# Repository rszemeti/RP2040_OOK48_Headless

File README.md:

# OOK48 Headless Serial + Desktop GUI

A modified RP2350/RP2040 OOK48 build where the touchscreen UI is replaced by a USB serial
control path and a desktop Python GUI.

All spectrum/waterfall rendering, operating controls, decode display, message management, and logging move to the PC GUI.

## Quick Links

- Latest release (download `.exe` / `.uf2`): https://github.com/rszemeti/RP2040_OOK48_Headless/releases/latest

## GUI (Front and Center)

The GUI is now the primary operator interface:

- **Live decode console** with RX/TX/error colouring and UTC timestamps
- **Contest TX pad** with dynamic templates (`{myCall}`, `{theirCall}`, `{serial}`, `{loc}`)
- **Confidence-aware decode pipeline** with unknown-gating and accumulator state display
- **Waterfall controls** (clip, auto-scale, clear) and decode mode quick-toggle
- **Persistent config** for callsign, timing, mode, and TX templates

---

## Performance vs Single-Repeat Decode

The firmware stream is effectively single-repeat per symbol period, but the GUI adds a
**soft-accumulator repeat** on top of that data:

- single-repeat characters are shown immediately (fast feedback)
- repeated cycles are accumulated per position and re-decoded with improved confidence
- unstable copy can be promoted to stable copy once mean confidence rises
- low-confidence runs auto-collapse and reset cleanly

This gives a practical improvement in weak/marginal conditions without changing the
core RF/FFT/radio processing code.

Current confidence gates used by the GUI accumulator:

- per-character unknown gate: `0.180` (below this, symbol is treated as unknown)
- confirmed-copy threshold: `0.65` (mean confidence)
- collapse threshold: `0.25` for `3` consecutive cycles

### Expected decode levels (measured)

Normal mode (good copy guideline):

- 1 repeat: `-17`
- 2 repeats: `-19`
- 4 repeats: `-20`
- 8 repeats: `-21`

Rainscatter mode (good copy guideline):

- 1 repeat: `+5 dB`
- 2 repeats: `+3 dB`
- 4 repeats: `+2 dB`
- 8 repeats: `+1.5 dB`

---

## Rainscatter Mode (Decode Mode 2)

`SET:decmode:2` enables **Rainscatter** mode, which uses wideband power behaviour
intended for bursty/scatter conditions rather than stable narrowband copy.

Operationally:

- firmware switches to decode mode `2`
- GUI can toggle Normal/Rainscatter from the RX pane button
- if connected firmware does not support mode `2`, GUI falls back to Normal safely

Use Rainscatter when copy is intermittent and burst-dominated; use Normal for steady
paths.

---

## What Changed From the Original

### Removed Entirely
- `config.ino` — replaced by serial `SET:` commands
- `GetApp.ino` — app selection now via `SET:app:`
- `MemPad.ino` — message slot selection now via `CMD:txmsg:`
- `TextPad.ino` — message text entry now via Python GUI
- `USBDrive.ino` — SD card logging is handled by the Python GUI instead
- All SD card hardware support (`SdFat`, `Adafruit_TinyUSB`, SPI1 setup)
- EEPROM read/write — settings are held in RAM and pushed from Python on connect
- Battery voltage measurement and calibration
- All touchscreen UI — buttons, config pages, keyboard, memory pad

### Modified
- `RP2040_OOK48_Serial.ino` — main file rewritten for RP2350/RP2040 targets: serial protocol added,
  `defaultSettings()` replaces EEPROM load/save, LCD init simplified
- `globals.h` — SD, battery, and EEPROM-specific variables removed;
  `core0Ready` flag added for core synchronisation
- `GUI.ino` — stripped to spectrum/waterfall/legend drawing only
- `DEFINES.h` — SD card pin definitions removed

### Unchanged
- `DMA.ino`, `FFT.ino`, `Rx.ino`, `Tx.ino`, `JT4Decode.ino`,
  `PI4Decode.ino`, `fano.ino` — all radio processing untouched

---

## How It Works

The RP2350/RP2040 enumerates as a USB CDC serial device (virtual COM port) when connected
to a laptop. The Python GUI connects to this port at 115200 baud.

On boot the firmware applies safe defaults and sends `RDY:<version>`. The Python
GUI responds by pushing all configuration settings. From that point on, decoded
messages stream out as simple prefixed ASCII lines and the GUI sends commands back
as needed.

The LCD shows the spectrum and waterfall continuously during RX, and a red TX
indicator during transmit — exactly as before, just without anything else on screen.

Protocol details for firmware/GUI integration are in `gui/ook48_serial_protocol.md`
and `Documents/ook48_serial_protocol.md`.

### Core-to-core FIFO char payload convention

To avoid races when Core 0 produces character events faster than Core 1 can consume them,
character-bearing FIFO messages are packed into one 32-bit word:

- low 16 bits: Core1Message command ID
- high 16 bits: associated character payload (8-bit char value)

Helpers are defined in `arduino/include/globals.h`:

- `FIFO_COMMAND(word)`
- `PACK_FIFO_CHAR(cmd, ch)`
- `UNPACK_FIFO_CHAR(word)`

Current packed char messages:

- `MORSEMESSAGE`
- `MESSAGE`
- `TMESSAGE`

This prevents shared-variable overwrite issues (for example, Morse CHAR followed quickly by WORD_SEP)
because command and payload travel atomically in the same FIFO entry.

---

## Firmware Releases (UF2)

For RP2350/RP2040 Pico-class targets, the easiest install format is **UF2** (not `avrdude`).

### RP2350 boards replacing RP2040

New Pico-compatible boards are increasingly RP2350-based and are generally the default choice now.
For this project, treat RP2350 as the modern replacement for RP2040: use the same UF2 workflow,
and keep using RP2040 hardware where already deployed.

### Download latest release assets

1. Open the project **Releases** page on GitHub:
  - https://github.com/rszemeti/RP2040_OOK48_Headless/releases/latest
2. Open the newest release (top of the list).
3. Under **Assets**, download:
  - `*.uf2` (firmware for the RP2350/RP2040 board)
  - `OOK48_GUI.exe` (Windows desktop GUI)

If Windows warns about SmartScreen, click **More info** → **Run anyway**.

### Flash UF2 to RP2350/RP2040 (BOOTSEL method)

1. Unplug the RP2350/RP2040 board from USB.
2. Press and hold the **BOOTSEL** button (some boards label this as **BOOT**).
3. While still holding BOOTSEL, plug the USB cable into the PC.
4. Release BOOTSEL after the board appears as a USB drive named **RPI-RP2**.
5. Drag/copy the downloaded `*.uf2` file onto that **RPI-RP2** drive.
6. Wait a few seconds; the drive disconnects automatically and the board reboots into the new firmware.

If your board has a separate **RESET/RUN** button, you typically still need to hold **BOOTSEL** (not RESET) during plug-in to enter UF2 bootloader mode.

---

### Windows 

The easiest solution for running the GUI on Winows is to download our "one file" release.

- `dist/OOK48_GUI.exe`

This is a prebuilt GUI instead of running all the Python stuff locally, just download `OOK48_GUI.exe` from the latest GitHub Release assets (see **Download latest release assets** above).

For local one-file builds with metadata stamping:

```powershell
.\scripts\build_gui_release.ps1
```

This script now auto-generates `assets/windows_version.txt` before calling PyInstaller.
Version fields are derived from Git (`tag`/`commit count`, with commit SHA/date in metadata comments).

## Python GUI

If you want to fiddle with the GUI and make changes, running the rawPython version is for you.

- **`ook48_gui.py`** — standard GUI with waterfall

### Requirements
```
pip install -r gui/requirements.txt
```

### Running
```
python ook48_gui.py
```

### Features

**Connection bar** — port selector, connect/disconnect, GPS time and locator
displayed live from `STA:` updates.

**Decode / TX tab** — split vertically into RX (left) and TX (right) panes.

- **RX pane** — colour-coded decode output: green=RX, red=TX echo, orange=error,
  dark green=JT4, purple=PI4, grey=system. Each message is prefixed with a UTC
  timestamp when its first character arrives. Double-clicking any received (green)
  word sets it as "Their call" in the TX pane.
  Clear button clears the screen only — the log file is unaffected.
  Save Log writes the current screen content to a file.

- **TX pane — Contest QSO pad** — designed for rapid contest operation:
  - **My call** — your callsign, persisted between sessions
  - **Their call** — type or double-click a received callsign to populate
  - **Serial #** — contest serial number with +1 button, persisted between sessions
  - All fields update the 10 slot buttons live as you type
  - **Single click** on any slot button immediately transmits that slot
  - **■ STOP TX** halts transmission and returns to RX

**TX message slots** — 10 slots are template-driven and rendered live from your
current operating fields.

The default slot template set:

| Slot | Content |
|------|---------|
| 0 | `CQ {myCall}` |
| 1 | `{theirCall} DE {myCall}` |
| 2 | `{theirCall} 59{serial} {loc}` |
| 3 | `{theirCall} 59{serial}` |
| 4 | `{loc}` |
| 5 | `ALL AGN` |
| 6 | `LOC AGN` |
| 7 | `RPT AGN` |
| 8 | `RGR 73` |
| 9 | `{myCall}` |

`{loc}` is substituted with live GPS locator data from `STA:`. Other substitutions are
rendered in the GUI before sending each slot to firmware.

Templates are user-editable in `ook48_config.json` (`messages[]`) and can be changed
without touching code.

**Settings tab** — all firmware parameters with Apply, Save, and Reboot buttons.

**File logging** — everything shown in the decode window is also written to
`ook48_YYYYMMDD.log` in the same directory, opened automatically on startup.
Multiple sessions on the same day append to the same file with a session marker.

### Waterfall (ook48_waterfall.py only)

A waterfall display sits above the decode text in the RX pane. It renders `WF:`
lines from the firmware as a scrolling thermal colour map (black → blue → cyan →
green → yellow → red).

- **Min / Max** spinboxes clip the colour range to the interesting signal level
- **Auto** sets Min/Max from the actual data range
- **Clear WF** clears the waterfall history
- **▶ Fake WF** generates synthetic test data at 9 rows/second — useful for
  testing the display without hardware connected

The waterfall adapts automatically to however many bins the firmware sends and
scales horizontally to fill the available window width.

### Config file (`ook48_config.json`)

Created automatically on first run. Persists port, callsign, serial number, and
all firmware settings between sessions. Example:

```json
{
  "port": "COM3",
  "callsign": "G4EML",
  "serial": 1,
  "gpsbaud": 9600,
  "loclen": 8,
  "decmode": 0,
  "txadv": 0,
  "rxret": 0,
  "halfrate": 0,
  "app": 0,
  "messages": [
    "CQ {myCall}",
    "{theirCall} DE {myCall}",
    "{theirCall} 59{serial} {loc}",
    "{theirCall} 59{serial}",
    "{loc}",
    "ALL AGN",
    "LOC AGN",
    "RPT AGN",
    "RGR 73",
    "{myCall}"
  ]
}
```

---

## Credits

- Colin Durbridge (G4EML) — original OOK48 work
- Robin Szemeti (G1YFG) — RP2040_OOK48_Headless (RP2350/RP2040) serial + GUI adaptation

---

## Notes

**GPS locator** — the locator shown in the connection bar is received from the
firmware via `STA:` lines and is used live in the TX slot buttons. If GPS has not
yet locked, `{LOC}` is passed through to the firmware for its own substitution.

**GPS baud rate** — `autoBaud()` detection is removed. The firmware starts at 9600
by default. If your GPS module runs at 38400, change `gpsbaud` in `ook48_config.json`
before first connect, or set it in the Settings tab and click Apply.

**First connect** — there is a 1.5 second delay after connecting before the config
push is sent, to allow the firmware time to finish booting and send its `RDY:` message.

**App switching** — changing the app via `SET:app:` causes an immediate reboot. The
Python GUI will show a disconnect; simply reconnect after a few seconds.

**TX echo** — transmitted characters are echoed back by the firmware as `TX:` lines
and appear in red in the decode window as they are actually sent, one character at
a time.

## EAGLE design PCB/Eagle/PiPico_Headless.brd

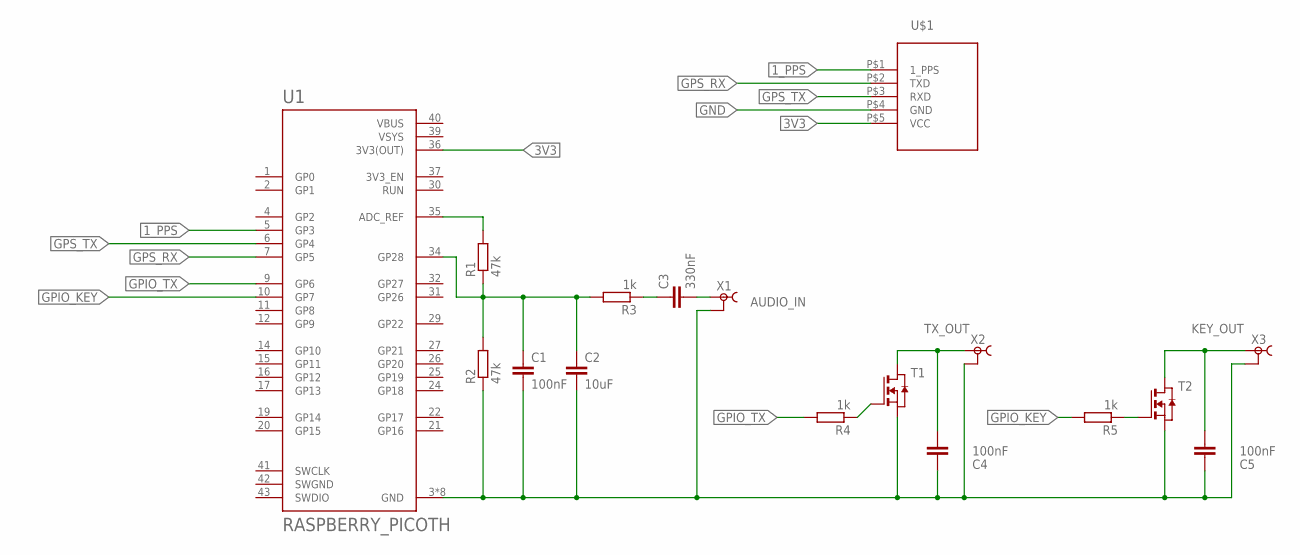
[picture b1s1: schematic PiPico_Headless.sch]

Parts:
C1, C4, C5: 100nF; C0805
C2: 10uF; C0805
C3: 330nF; C0805
R1, R2: 47k; R0805
R3, R4, R5: 1k; R0805
T1, T2: NMOSSOT23; SOT-23
U1: RASPBERRY_PICOTH; PICO-PKG-TH
U$1: GPS
X1: AUDIO_IN; TOBU3
X2: TX_OUT; TOBU3
X3: KEY_OUT; TOBU3; MPN TOBU 3

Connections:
1_PPS: U1.5 (GP3), U$1.P$1 (1_PPS)
3V3: U1.36 (3V3(OUT)), U$1.P$5 (VCC)
GND: C1.2, C2.2, C4.1, C5.1, R2.1, T1.2 (S), T2.2 (S), U1.3 (GND), U1.8 (GND), U1.13 (GND), U1.18 (GND), U1.23 (GND), U1.28 (GND), U1.33 (GND), U1.38 (GND), U$1.P$4 (GND), X1.2, X1.2@1 (2), X1.2@2 (2), X2.2, X2.2@1 (2), X2.2@2 (2), X3.2, X3.2@1 (2), X3.2@2 (2)
GPIO_KEY: R5.2, U1.10 (GP7)
GPIO_TX: R4.2, U1.9 (GP6)
GPS_RX: U1.7 (GP5), U$1.P$2 (TXD)
GPS_TX: U1.6 (GP4), U$1.P$3 (RXD)
unnamed: C1.1, C2.1, R1.1, R2.2, R3.2, U1.34 (GP28)
unnamed: R5.1, T2.3 (G)
unnamed: R1.2, U1.35 (ADC_REF)
unnamed: C3.1, R3.1
unnamed: C3.2, X1.1
unnamed: R4.1, T1.3 (G)
unnamed: C4.2, T1.1 (D), X2.1
unnamed: C5.2, T2.1 (D), X3.1
SWGND: U1.42 (SWGND)
VBUS: U1.40 (VBUS)
VSYS: U1.39 (VSYS)

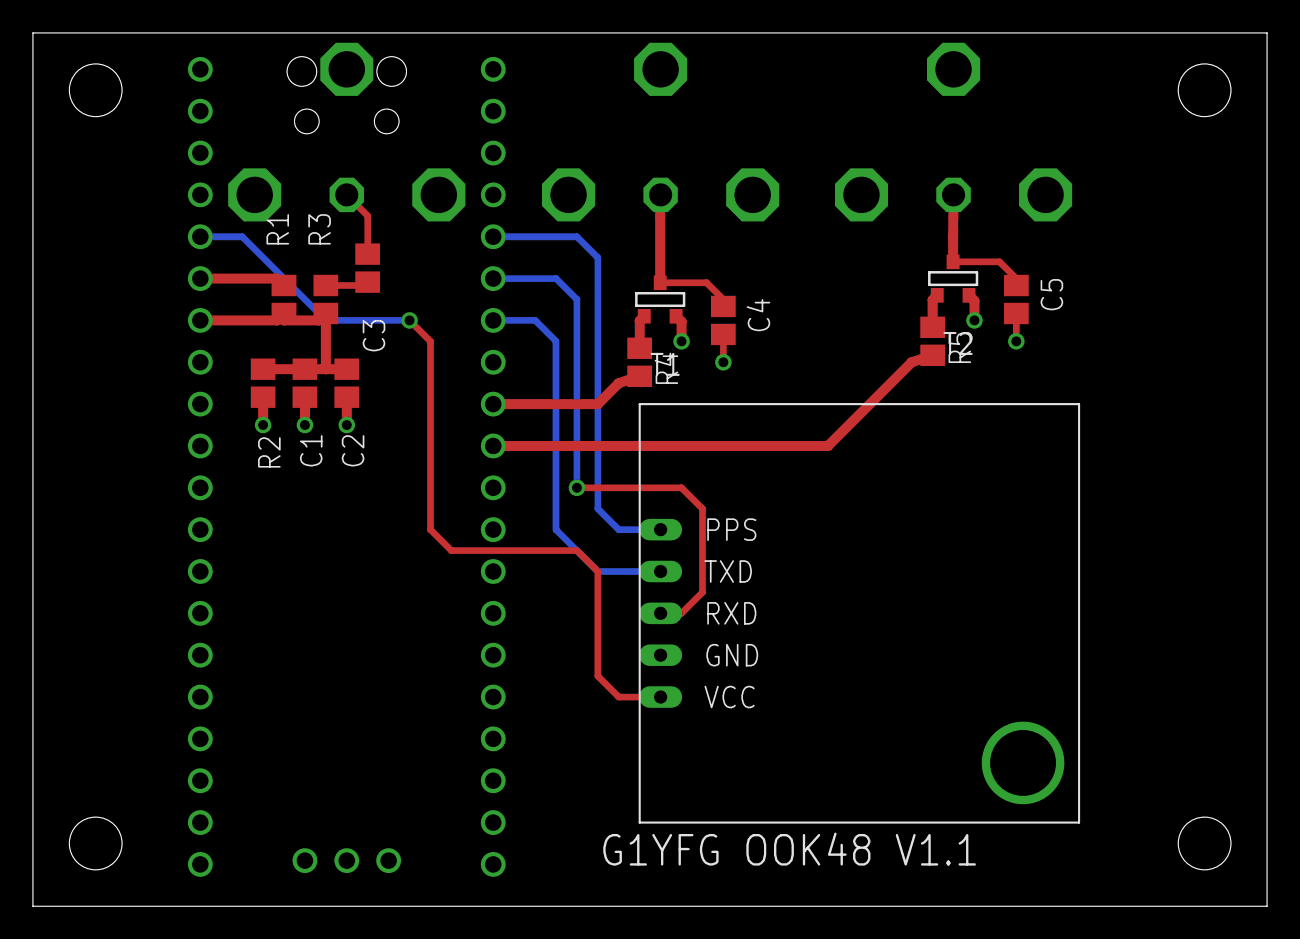
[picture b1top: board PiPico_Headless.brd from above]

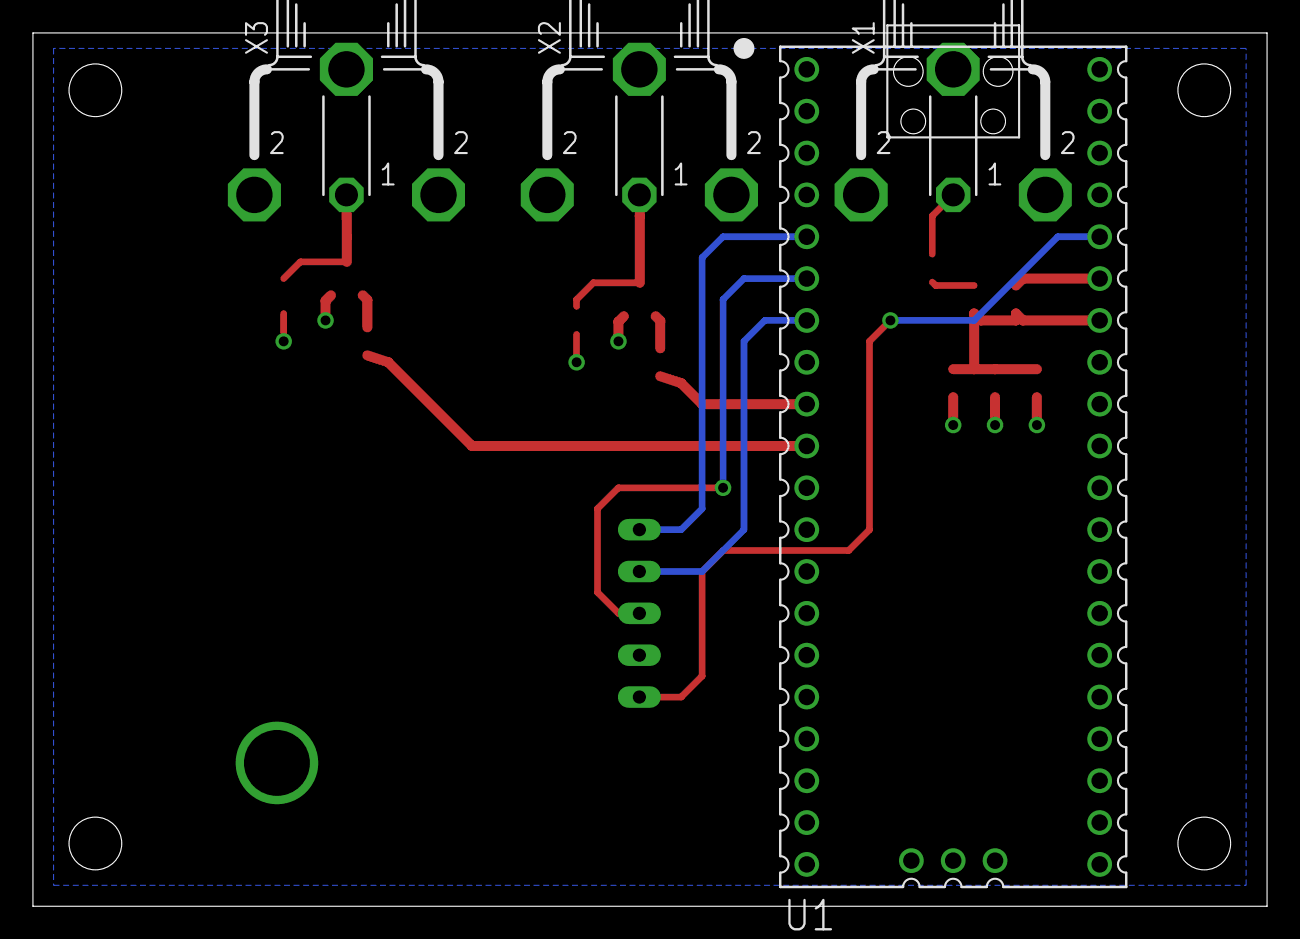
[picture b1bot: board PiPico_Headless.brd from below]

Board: 2 copper layers, 74.9 x 53.0 mm, 17 parts (4 on the bottom side), 15 nets.

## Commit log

2025-09-29 Update PCB
2025-10-01 More Beacon Mode
2025-10-01 More Beacon Stuff
2025-10-03 More Beacon Decoder
2025-10-04 More BEacon Decoder Work
2025-10-05 Fix Sampling rates
2025-10-06 Beacon Mode Now Working!!!!
2025-10-06 Fix SD card saving
2025-10-07 Allow menu selection of app
2025-10-07 Add coloured app buttons
2025-10-10 Add SunShade
2026-02-24 Test file generator
    some test files with bandwidth limited noise at various SNR levels
2026-02-24 Initial stab at a GUI
2026-02-25 a bit more GUI ...
2026-02-25 First stab at the Arduino stuff ...
2026-02-25 basic live waterfall ...
2026-02-25 Better updates on GUI + simulator
2026-02-26 Slight improvements to GUI and simulator
2026-02-26 Initial Platformio build
2026-02-26 Initial accumulator rework
2026-02-26 GUI with "accumulator"
    also added protocol document
2026-02-26 Add GPS_DEFAULT_BAUD define, confidence threshold setting, RX audio level indicator, CMD:ident for firmware version, remove gpsBaud from settings struct and serial protocol
2026-02-26 Add .gitignore: exclude pycache, json config and log files; untrack ook48_config.json
2026-02-26 Add gui/.gitignore to exclude json and log files
2026-02-26 Bring Test Files Python scripts from analysis
2026-02-26 Add rainscatter decode mode (decmode 2)
2026-02-26 Add rainscatter no-carrier power-step test harness
2026-02-26 Extend rainscatter harness for long x8 accumulation tests
2026-02-26 Add rainscatter mode UI/docs and test harness refinements
2026-02-26 Add confidence-threshold tooling, GUI hookup, and docs assets
2026-02-26 Use main-tab decode toggle button instead of checkbox
2026-02-26 Release: GUI updates, docs refresh, and Windows one-file EXE
2026-02-26 chore: tighten gitignore for build and test artifacts
2026-02-26 feat: automate UF2 firmware releases and BOOTSEL flasher
2026-02-27 Added send dashed, and UF2 release build
2026-02-27 Update README.md
    added easy flashing instructions
2026-02-27 docs: simplify README and align RP2350/RP2040 wording
2026-02-27 docs: fix GUI dependency installation instructions
2026-02-27 gui: reduce ACK log noise and keep command acks
2026-02-28 Added morse sending to GUI and firmware
    Also added initial work on morse decoder
2026-02-28 Removed some generated test wavs
2026-02-28 Initial PCB and catchup
2026-03-01 First stab at porting the morse to .cpp
    Morse decoder, reads OK down to -15dB SNR
    Takes a couple of char to correctly lock up,
    tested from 6wpm to 20wpm
    tested with drifting carriers and with simulated QSB
2026-03-01 Initial "Morse" release
    With improved GUI and "rainscatter" mode for morse.
2026-03-01 V1.1 release
2026-03-08 Fixed a FIFO race condition
2026-03-08 fw version number update
2026-03-08 Attempt to automate GUI build in release workflow
2026-03-10 V1.0 PCB
2026-03-10 Updated PCB
2026-03-10 Track correction on PCB, GPS Status
    corrected track on PCB (RX/TX swap)
    Added GPS debug and GPS tab to UI
